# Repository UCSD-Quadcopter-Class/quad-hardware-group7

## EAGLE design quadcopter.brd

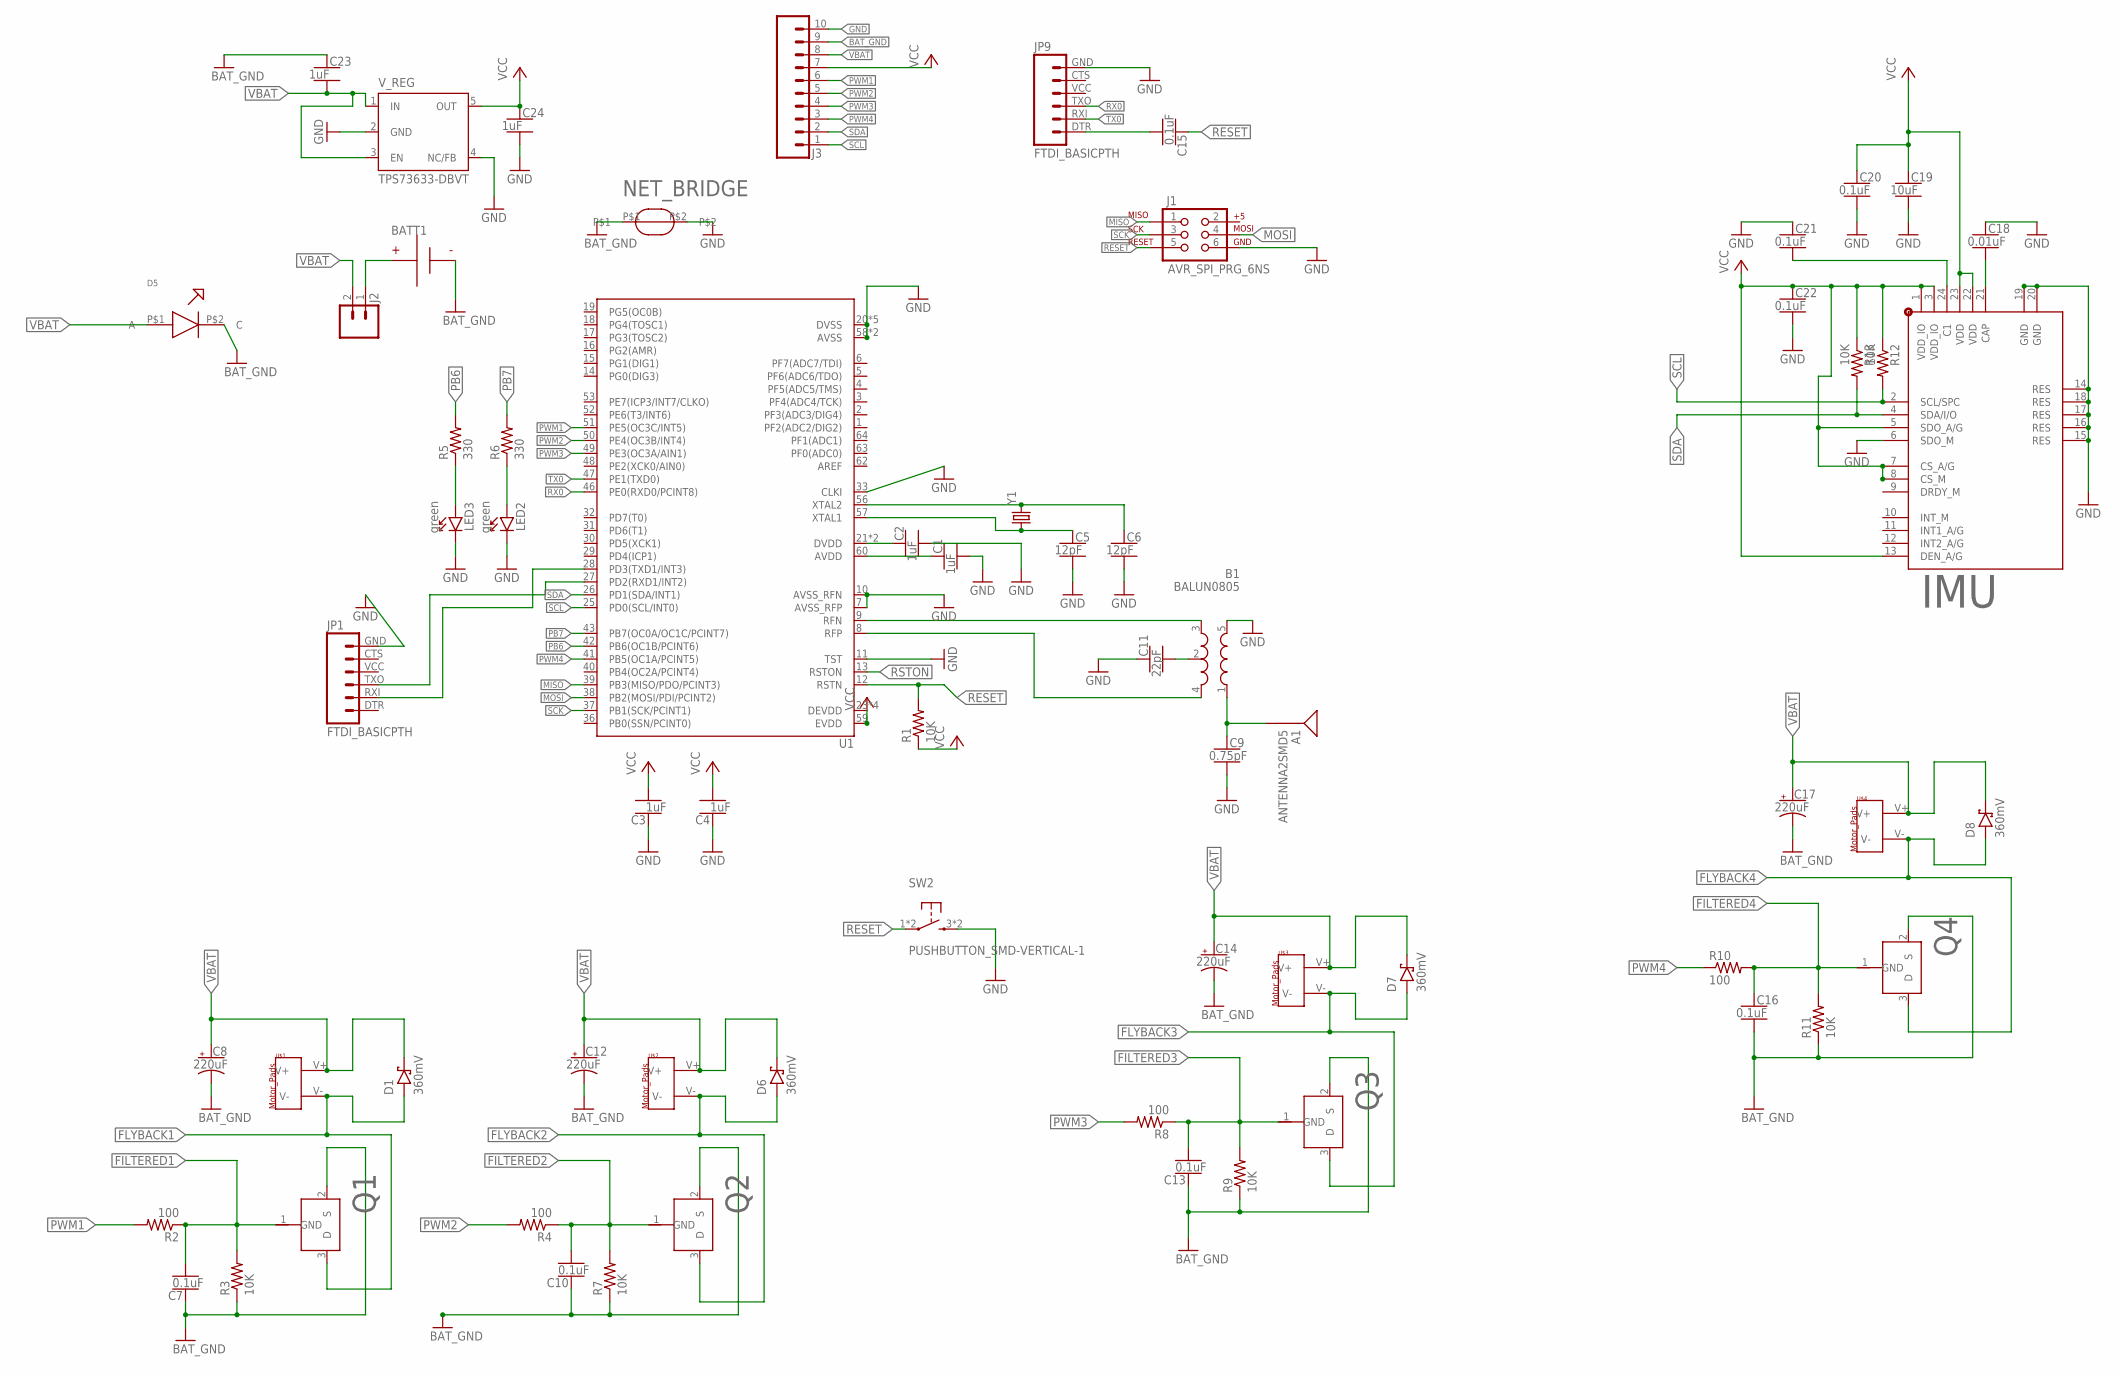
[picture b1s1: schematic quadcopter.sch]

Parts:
A1: ANTENNA2SMD5; ANTENNA-CHIP5
B1: BALUN0805; BALUN
BATT1: BATTERY-HUBSAN-W/HOLDER; BATTERY-W/HOLDER-380MAH-HUBSAN
C1, C2, C3, C4, C23, C24: 1uF; CAPC2012X140_HS
C5, C6: 12pF; CAPC2012X140_HS
C7, C10, C13, C15, C16, C20, C21, C22: 0.1uF; CAPC2012X140_HS
C8, C12, C14, C17: 220uF; CAPMP7343X310_HS
C9: 0.75pF; CAPC2012X140_HS
C11: 22pF; CAPC2012X140_HS
C18: 0.01uF; CAPC2012X140_HS
C19: 10uF; CAPC2012X140_HS
D1, D6, D7, D8: 360mV; SOD3716X135_HS
D5: BLUE_LED
IMU: 9-AXIS_IMU
J1: AVR_SPI_PRG_6NS; 2X3-NS
J2: MALE_HEADER_2POS-2X1-0.1IN; MALE_HEADER_2X1_0.1IN
J3: SIP-10_TH-254X10; HDRV10W63P254_10X1_2540X254H838_HS
JP1, JP9: FTDI_BASICPTH; FTDI_BASIC
LED2, LED3: green; LEDSC125X200X120-2_HS
NET_BRIDGE: NET_BRIDGE
Q1, Q2, Q3, Q4: N-CHANNEL_MOSFET
R1, R3, R7, R9, R11, R12, R13: 10K; RESC2012X60_HS
R2, R4, R8, R10: 100; RESC2012X60_HS
R5, R6: 330; RESC2012X60_HS
SW2: PUSHBUTTON_SMD-VERTICAL-1; TE_FSM8JSMA_HS
U1: ATMEGA128RFA1; QFN-64
U$1, U$2, U$3, U$4: MOTOR_PADS
V_REG: TPS73633-DBVT; SOT23-DBV
Y1: CRYSTAL5X3; CRYSTAL-SMD-5X3

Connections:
BAT_GND: BATT1.- (N), C7.1, C8.2 (-), C10.1, C12.2 (-), C13.1, C14.2 (-), C16.2, C17.2 (-), C23.1, D5.P$2 (C), J3.9, NET_BRIDGE.P$1, Q1.2 (S), Q2.2 (S), Q3.2 (S), Q4.2 (S), R3.1, R7.1, R9.1, R11.1
FILTERED1: C7.2, Q1.1 (GND), R2.1, R3.2
FILTERED2: C10.2, Q2.1 (GND), R4.1, R7.2
FILTERED3: C13.2, Q3.1 (GND), R8.1, R9.2
FILTERED4: C16.1, Q4.1 (GND), R10.2, R11.2
FLYBACK1: D1.A, Q1.3 (D), U$1.V-
FLYBACK2: D6.A, Q2.3 (D), U$2.V-
FLYBACK3: D7.A, Q3.3 (D), U$3.V-
FLYBACK4: D8.A, Q4.3 (D), U$4.V-
GND: B1.5 (GND), C1.2, C2.2, C3.1, C4.1, C5.2, C6.2, C9.2, C11.1, C18.1, C19.2, C20.2, C21.1, C22.2, C24.2, IMU.6 (SDO_M), IMU.14 (RES), IMU.15 (RES), IMU.16 (RES), IMU.17 (RES), IMU.18 (RES), IMU.19 (GND), IMU.20 (GND), J1.6, J3.10, JP1.GND (6), JP9.GND (6), LED2.C, LED3.C, NET_BRIDGE.P$2, SW2.3 (2), SW2.4 (2), U1.7 (AVSS_RFP), U1.10 (AVSS_RFN), U1.11 (TST), U1.20 (DVSS), U1.24 (DVSS), U1.33 (CLKI), U1.35 (DVSS), U1.45 (DVSS), U1.55 (DVSS), U1.58 (AVSS), U1.61 (AVSS), V_REG.2 (GND), V_REG.4 (NC/FB)
MISO: J1.1, U1.39 (PB3(MISO/PDO/PCINT3))
MOSI: J1.4, U1.38 (PB2(MOSI/PDI/PCINT2))
unnamed: C5.1, U1.57 (XTAL1), Y1.1
unnamed: C2.1, U1.21 (DVDD), U1.22 (DVDD)
unnamed: B1.3 (OUT2), U1.9 (RFN)
unnamed: C1.1, U1.60 (AVDD)
unnamed: B1.4 (OUT1), U1.8 (RFP)
unnamed: C6.1, U1.56 (XTAL2), Y1.3 (2)
unnamed: B1.2 (GND), C11.2
unnamed: A1.FEED, B1.1 (IN), C9.1
unnamed: JP1.TXO (3), U1.27 (PD2(RXD1/INT2))
unnamed: LED3.A, R5.1
unnamed: LED2.A, R6.1
unnamed: JP1.RXI (2), U1.28 (PD3(TXD1/INT3))
unnamed: C18.2, IMU.21 (CAP)
unnamed: C15.2, JP9.DTR (1)
unnamed: C21.2, IMU.24 (C1)
unnamed: BATT1.+, J2.1
PB6: R5.2, U1.42 (PB6(OC1B/PCINT6))
PB7: R6.2, U1.43 (PB7(OC0A/OC1C/PCINT7))
PWM1: J3.6, R2.2, U1.51 (PE5(OC3C/INT5))
PWM2: J3.5, R4.2, U1.50 (PE4(OC3B/INT4))
PWM3: J3.4, R8.2, U1.49 (PE3(OC3A/AIN1))
PWM4: J3.3, R10.1, U1.41 (PB5(OC1A/PCINT5))
RESET: C15.1, J1.5, R1.2, SW2.1, SW2.2 (1), U1.12 (RSTN)
RSTON: U1.13 (RSTON)
RX0: JP9.TXO (3), U1.46 (PE0(RXD0/PCINT8))
SCK: J1.3, U1.37 (PB1(SCK/PCINT1))
SCL: IMU.2 (SCL/SPC), J3.1, R12.2, U1.25 (PD0(SCL/INT0))
SDA: IMU.4 (SDA/I/O), J3.2, R13.2, U1.26 (PD1(SDA/INT1))
TX0: JP9.RXI (2), U1.47 (PE1(TXD0))
VBAT: C8.1 (+), C12.1 (+), C14.1 (+), C17.1 (+), C23.2, D1.C, D5.P$1 (A), D6.C, D7.C, D8.C, J2.2, J3.8, U$1.V+, U$2.V+, U$3.V+, U$4.V+, V_REG.1 (IN), V_REG.3 (EN)
VCC: C3.2, C4.2, C19.1, C20.1, C22.1, C24.1, IMU.1 (VDD_IO), IMU.3 (VDD_IO), IMU.5 (SDO_A/G), IMU.7 (CS_A/G), IMU.8 (CS_M), IMU.13 (DEN_A/G), IMU.22 (VDD), IMU.23 (VDD), J3.7, R1.1, R12.1, R13.1, U1.23 (DEVDD), U1.34 (DEVDD), U1.44 (DEVDD), U1.54 (DEVDD), U1.59 (EVDD), V_REG.5 (OUT)

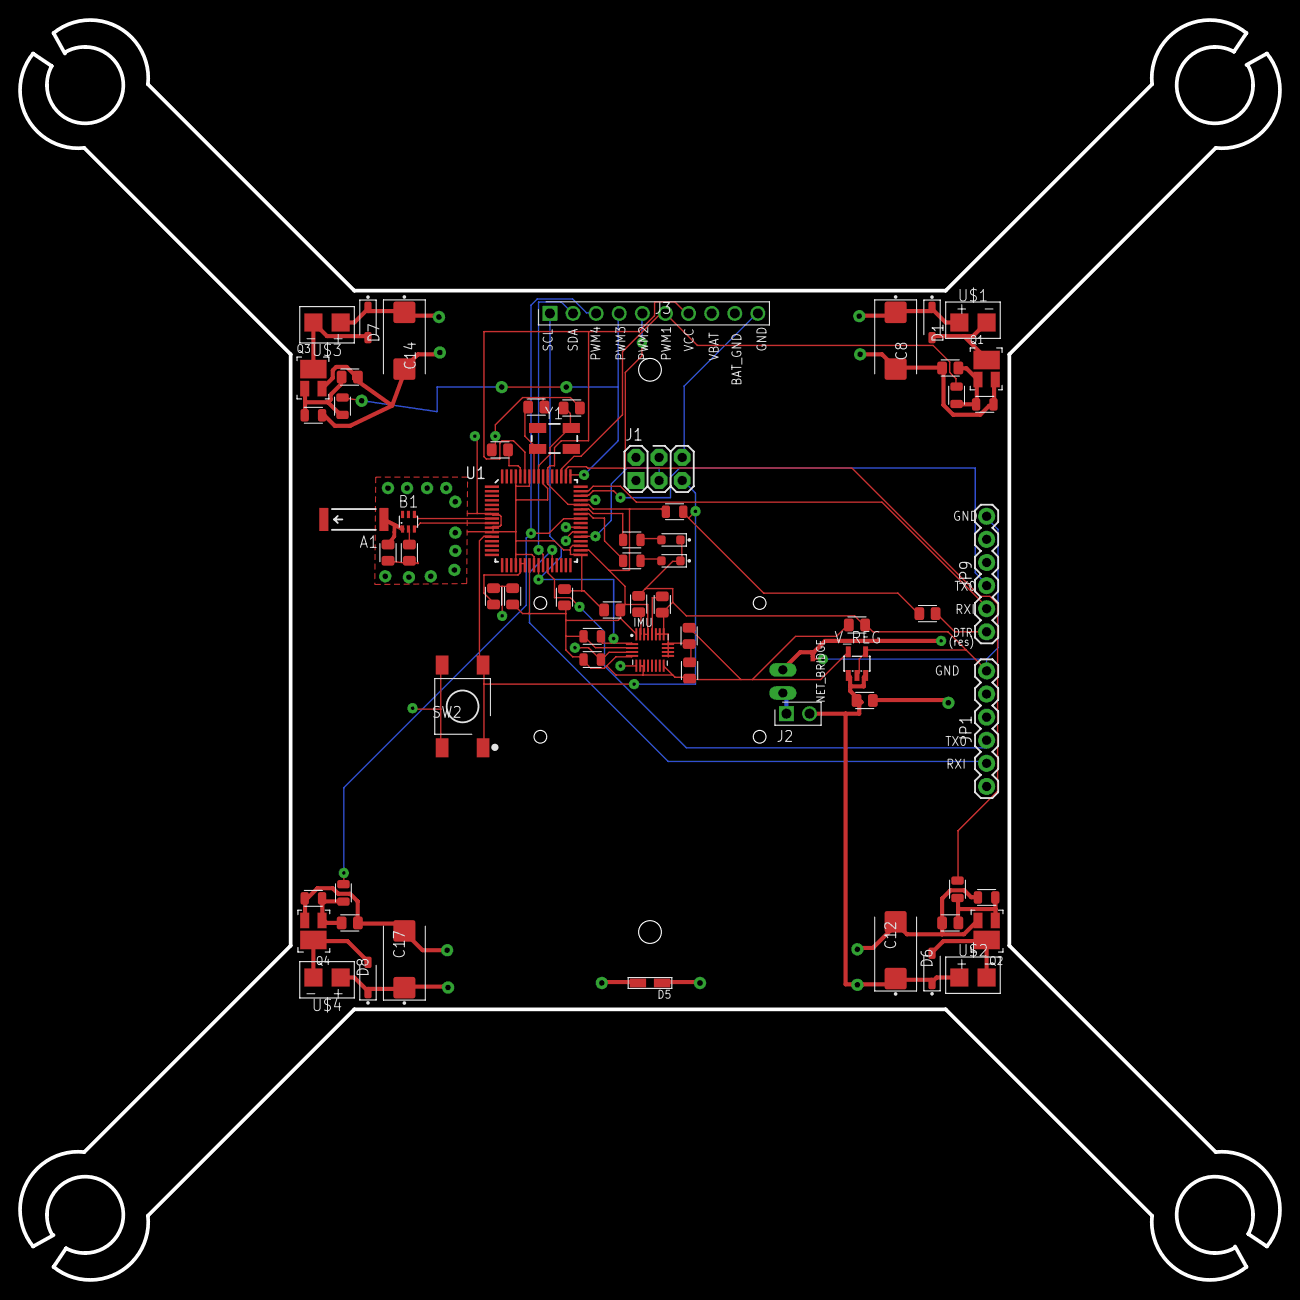
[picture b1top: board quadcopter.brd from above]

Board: 4 copper layers, 138.5 x 138.5 mm, 66 parts (1 on the bottom side), 42 nets.

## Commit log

2017-04-18 Added redboard sch and board
2017-04-18 added my own quadparts (john)
2017-04-18 Added quadparts-nick
2017-04-18 moved quadparts to lbr
2017-04-18 most work done on quadcopter.sch
2017-04-18 Added breakout header and power-supply parts
2017-04-20 Hooked up power supply, fixed some connections on IMU
2017-04-20 fixed a few nets
2017-04-20 added who_am_i
2017-04-23 Added Blue LED
2017-04-23 Added LED to design
2017-04-23 Added frame and moved all parts in schematic to fit the frame
2017-04-23 fixed gnd->bat_gnd for all motor parts. also flipped source and drain
2017-04-25 Made all the review changes
2017-04-25 Enlarged mosfet pads per profs recommendation
2017-04-26 Fixed tStop for pads in the IMU
2017-04-27 instructior review of original schematic
2017-04-27 Made changes according to Profs feedback
2017-04-30 updated quadcopter.sch libraries
2017-04-30 created dimensions of board and added design rules
2017-05-01 Did board work, renamed flyback and filtered in schematic
2017-05-01 board before auto-routing
2017-05-01 Routed and manually connected most wires. Waiting on piazza question before connecting the last few
2017-05-02 finished routing
2017-05-04 Commiting before the autorouter ruins e verything
2017-05-04 Autorouting complete after review
2017-05-04 Added reviews of our group and theirs
2017-05-04 Fixed location of items
2017-05-04 Added additional 2mm to arm lengths"
2017-05-05 Changed ground on LED to batgnd"
2017-05-09 Board passes DFM
2017-05-09 Approved all DRC checks in board. renamed files to fit naming convention for lab8"
2017-05-10 Board design review 1
2017-05-11 Made most of swanson changes. Did not add reset button yet and did not autoroute and did not add in holes yet
2017-05-12 added reset button and did autorouting
2017-05-14 more schematic comments from swanson
2017-05-15 Made all changes specified in design review. Except LED
2017-05-15 Changed the resistor and capacitor placements in the motor drivers
2017-05-16 Oriented all GND and VCC symbols in the sch correctly
2017-05-16 commented on sch review
2017-05-16 Fix gnd/bat_gnd issue and re ran cam job
2017-05-16 removed sub dir
